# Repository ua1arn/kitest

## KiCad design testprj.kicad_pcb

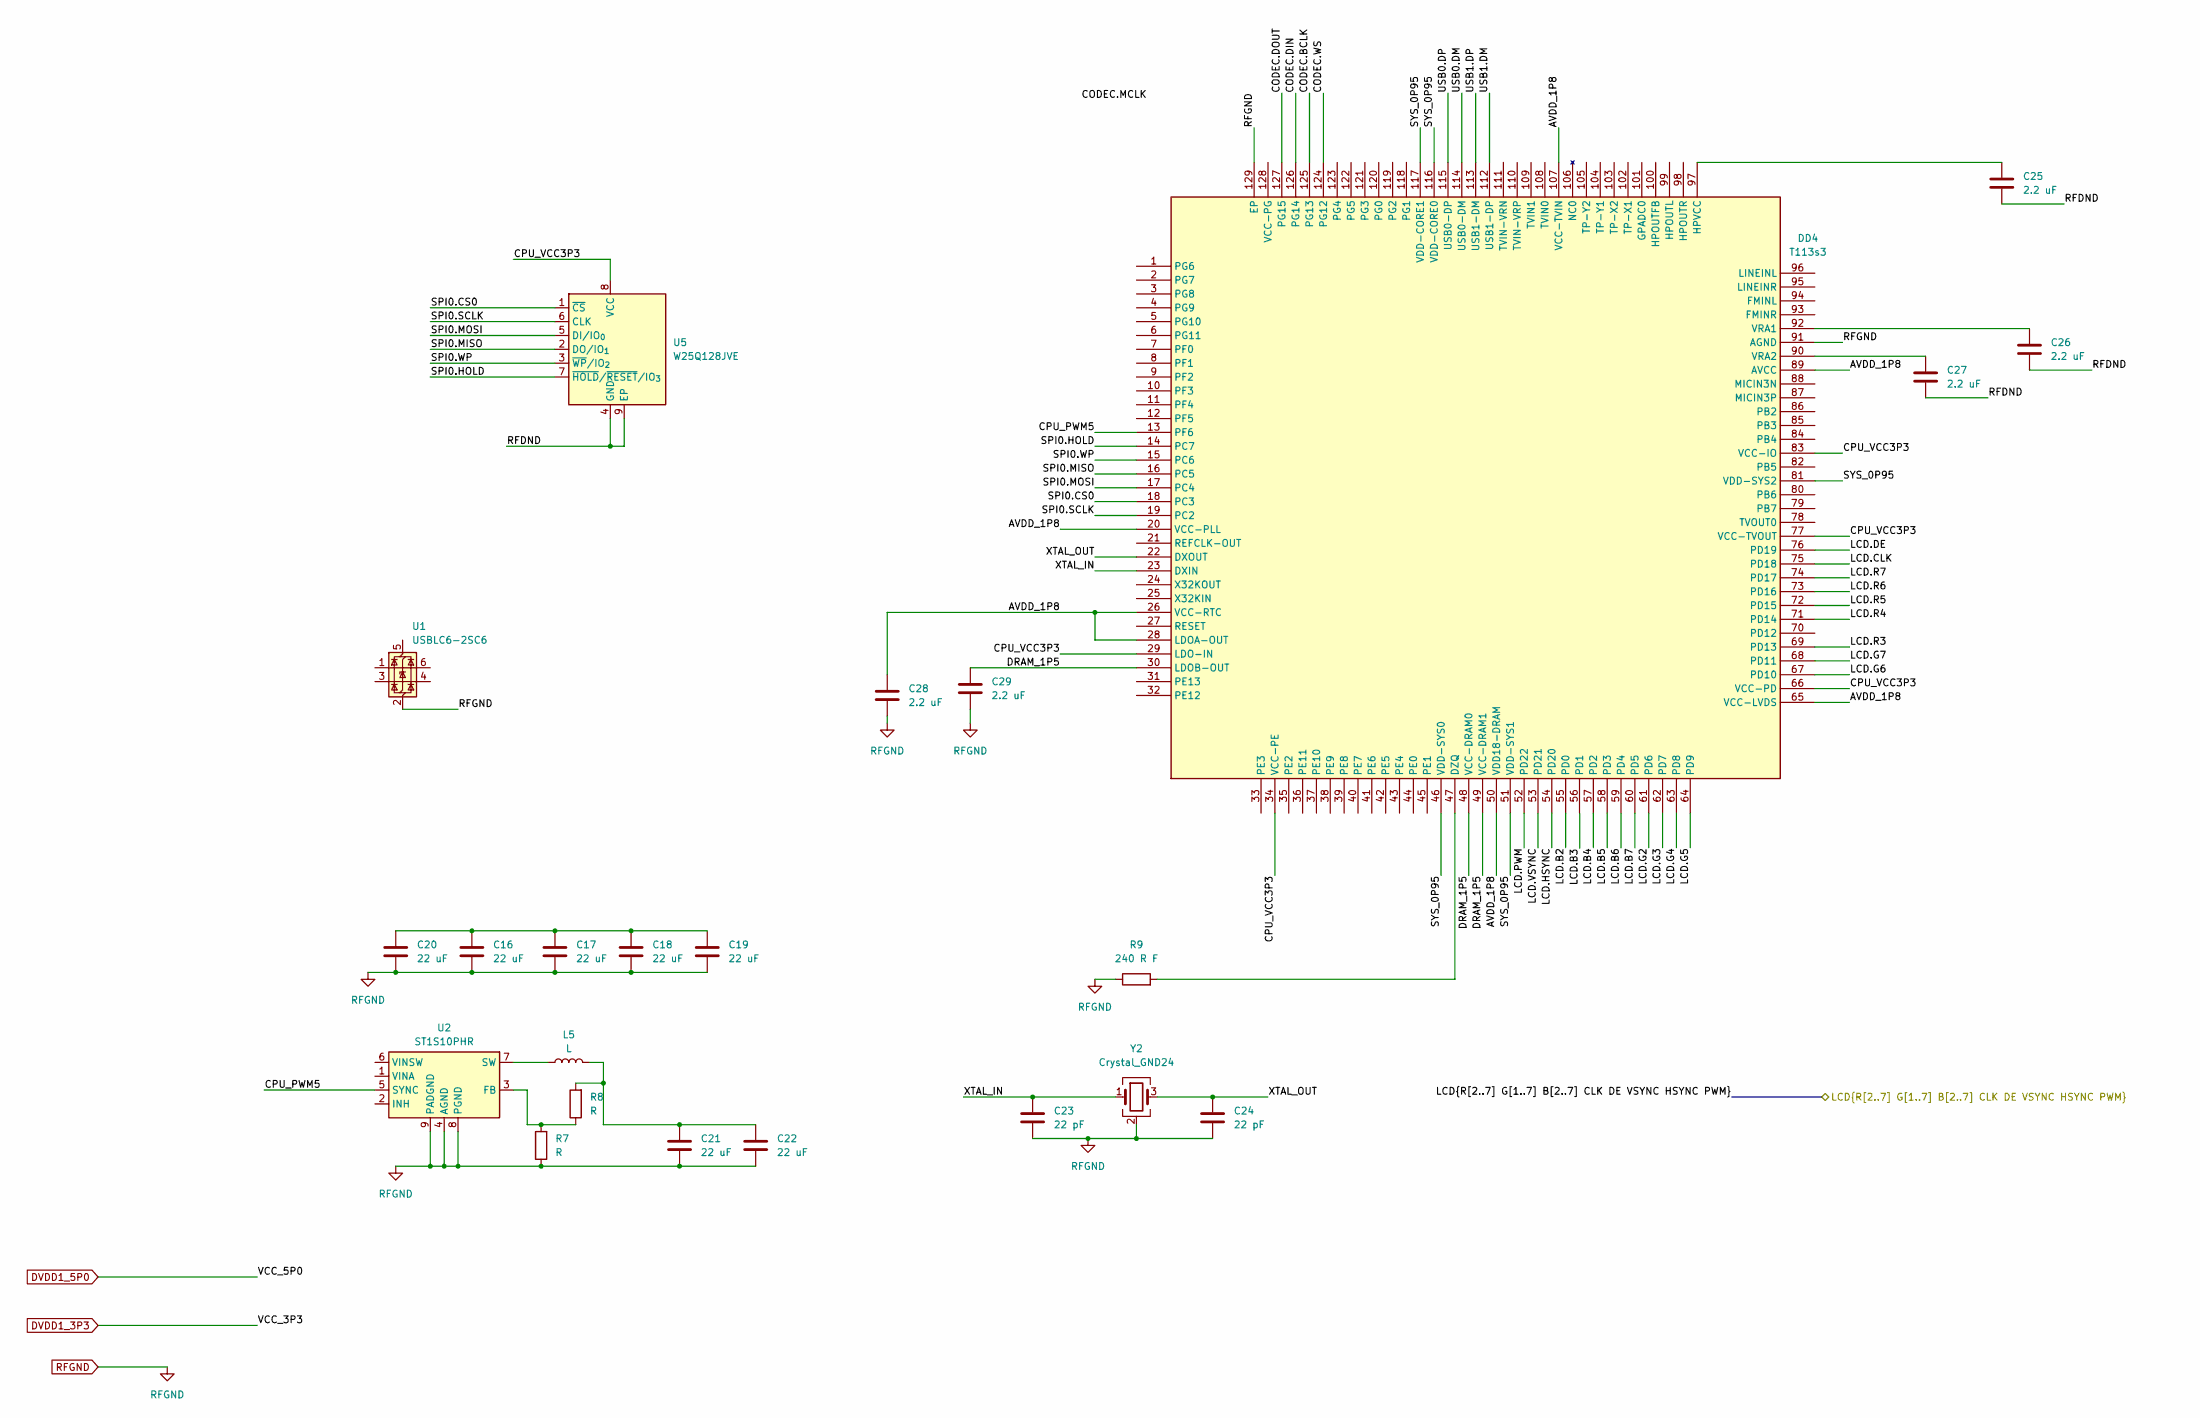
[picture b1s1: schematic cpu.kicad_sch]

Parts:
C16, C17, C18, C19, C20, C21, C22: 22 uF; C_1206_3216Metric_Pad1.33x1.80mm_HandSolder
C23, C24: 22 pF; C_0805_2012Metric_Pad1.18x1.45mm_HandSolder
C25, C26, C27, C28, C29: 2.2 uF; C_0805_2012Metric_Pad1.18x1.45mm_HandSolder
DD4: T113s3; TQFP-128_14x14mm_P0.4mm_EP8x8mm
L5: L; L_TDK_VLS6045EX_VLS6045AF
R7, R8: R; R_0805_2012Metric_Pad1.20x1.40mm_HandSolder
R9: 240 R F; R_0805_2012Metric_Pad1.20x1.40mm_HandSolder
U1: USBLC6-2SC6; SOT-23-6
U2: ST1S10PHR; TI_SO-PowerPAD-8
U5: W25Q128JVE; WSON-8-1EP_8x6mm_P1.27mm_EP3.4x4.3mm
Y2: Crystal_GND24; Crystal_SMD_7050-4Pin_7.0x5.0mm

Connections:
/cpu/AVDD_1P8: C28.1, DD4.20 (VCC-PLL), DD4.26 (VCC-RTC), DD4.28 (LDOA-OUT), DD4.50 (VDD18-DRAM), DD4.65 (VCC-LVDS), DD4.89 (AVCC), DD4.107 (VCC-TVIN)
/cpu/CODEC.BCLK: DD4.125 (PG13)
/cpu/CODEC.DIN: DD4.126 (PG14)
/cpu/CODEC.DOUT: DD4.127 (PG15)
/cpu/CODEC.WS: DD4.124 (PG12)
/cpu/CPU_PWM5: DD4.13 (PF6), U2.5 (SYNC)
/cpu/CPU_VCC3P3: DD4.29 (LDO-IN), DD4.34 (VCC-PE), DD4.66 (VCC-PD), DD4.77 (VCC-TVOUT), DD4.83 (VCC-IO), U5.8 (VCC)
/cpu/DRAM_1P5: C29.1, DD4.30 (LDOB-OUT), DD4.48 (VCC-DRAM0), DD4.49 (VCC-DRAM1)
/cpu/LCD.B4: DD4.57 (PD2); also elsewhere on the board
/cpu/LCD.B5: DD4.58 (PD3); also elsewhere on the board
/cpu/LCD.B6: DD4.59 (PD4); also elsewhere on the board
/cpu/LCD.B7: DD4.55 (PD0), DD4.60 (PD5); also elsewhere on the board
/cpu/LCD.CLK: DD4.75 (PD18); also elsewhere on the board
/cpu/LCD.DE: DD4.76 (PD19); also elsewhere on the board
/cpu/LCD.G2: DD4.61 (PD6); also elsewhere on the board
/cpu/LCD.G3: DD4.62 (PD7); also elsewhere on the board
/cpu/LCD.G4: DD4.63 (PD8); also elsewhere on the board
/cpu/LCD.G5: DD4.64 (PD9); also elsewhere on the board
/cpu/LCD.G6: DD4.67 (PD10); also elsewhere on the board
/cpu/LCD.G7: DD4.68 (PD11); also elsewhere on the board
/cpu/LCD.HSYNC: DD4.54 (PD20); also elsewhere on the board
/cpu/LCD.PWM: DD4.52 (PD22); also elsewhere on the board
/cpu/LCD.R3: DD4.69 (PD13); also elsewhere on the board
/cpu/LCD.R4: DD4.71 (PD14); also elsewhere on the board
/cpu/LCD.R5: DD4.72 (PD15); also elsewhere on the board
/cpu/LCD.R6: DD4.73 (PD16); also elsewhere on the board
/cpu/LCD.R7: DD4.74 (PD17); also elsewhere on the board
/cpu/LCD.VSYNC: DD4.53 (PD21); also elsewhere on the board
/cpu/RFDND: C25.2, C26.2, C27.2, U5.4 (GND), U5.9 (EP)
/cpu/SPI0.CS0: DD4.18 (PC3), U5.1 (~CS)
/cpu/SPI0.HOLD: DD4.14 (PC7), U5.7 (~HOLD/~RESET/IO_{3})
/cpu/SPI0.MISO: DD4.16 (PC5), U5.2 (DO/IO_{1})
/cpu/SPI0.MOSI: DD4.17 (PC4), U5.5 (DI/IO_{0})
/cpu/SPI0.SCLK: DD4.19 (PC2), U5.6 (CLK)
/cpu/SPI0.WP: DD4.15 (PC6), U5.3 (~WP/IO_{2})
/cpu/SYS_0P95: DD4.46 (VDD-SYS0), DD4.51 (VDD-SYS1), DD4.81 (VDD-SYS2), DD4.116 (VDD-CORE0), DD4.117 (VDD-CORE1)
/cpu/USB0.DM: DD4.114 (USB0-DM)
/cpu/USB0.DP: DD4.115 (USB0-DP)
/cpu/USB1.DM: DD4.112 (USB1-DP)
/cpu/USB1.DP: DD4.113 (USB1-DM)
/cpu/XTAL_IN: C23.1, DD4.23 (DXIN), Y2.1
/cpu/XTAL_OUT: C24.1, DD4.22 (DXOUT), Y2.3
unnamed: C16.2, C17.2, C18.2, C19.2, C20.2
unnamed: C21.2, C22.2, L5.2, R8.2
unnamed: DD4.47 (DZQ), R9.2
unnamed: C25.1, DD4.97 (HPVCC)
unnamed: C26.1, DD4.92 (VRA1)
unnamed: C27.1, DD4.90 (VRA2)
unnamed: R7.2, R8.1, U2.3 (FB)
unnamed: L5.1, U2.7 (SW)
RFGND: C16.1, C17.1, C18.1, C19.1, C20.1, C21.1, C22.1, C23.2, C24.2, C28.2, C29.2, DD4.91 (AGND), DD4.129 (EP), R7.1, R9.1, U1.2 (GND_2), U2.4 (AGND), U2.8 (PGND), U2.9 (PADGND), Y2.2 (G), Y2.4 (G); also elsewhere on the board

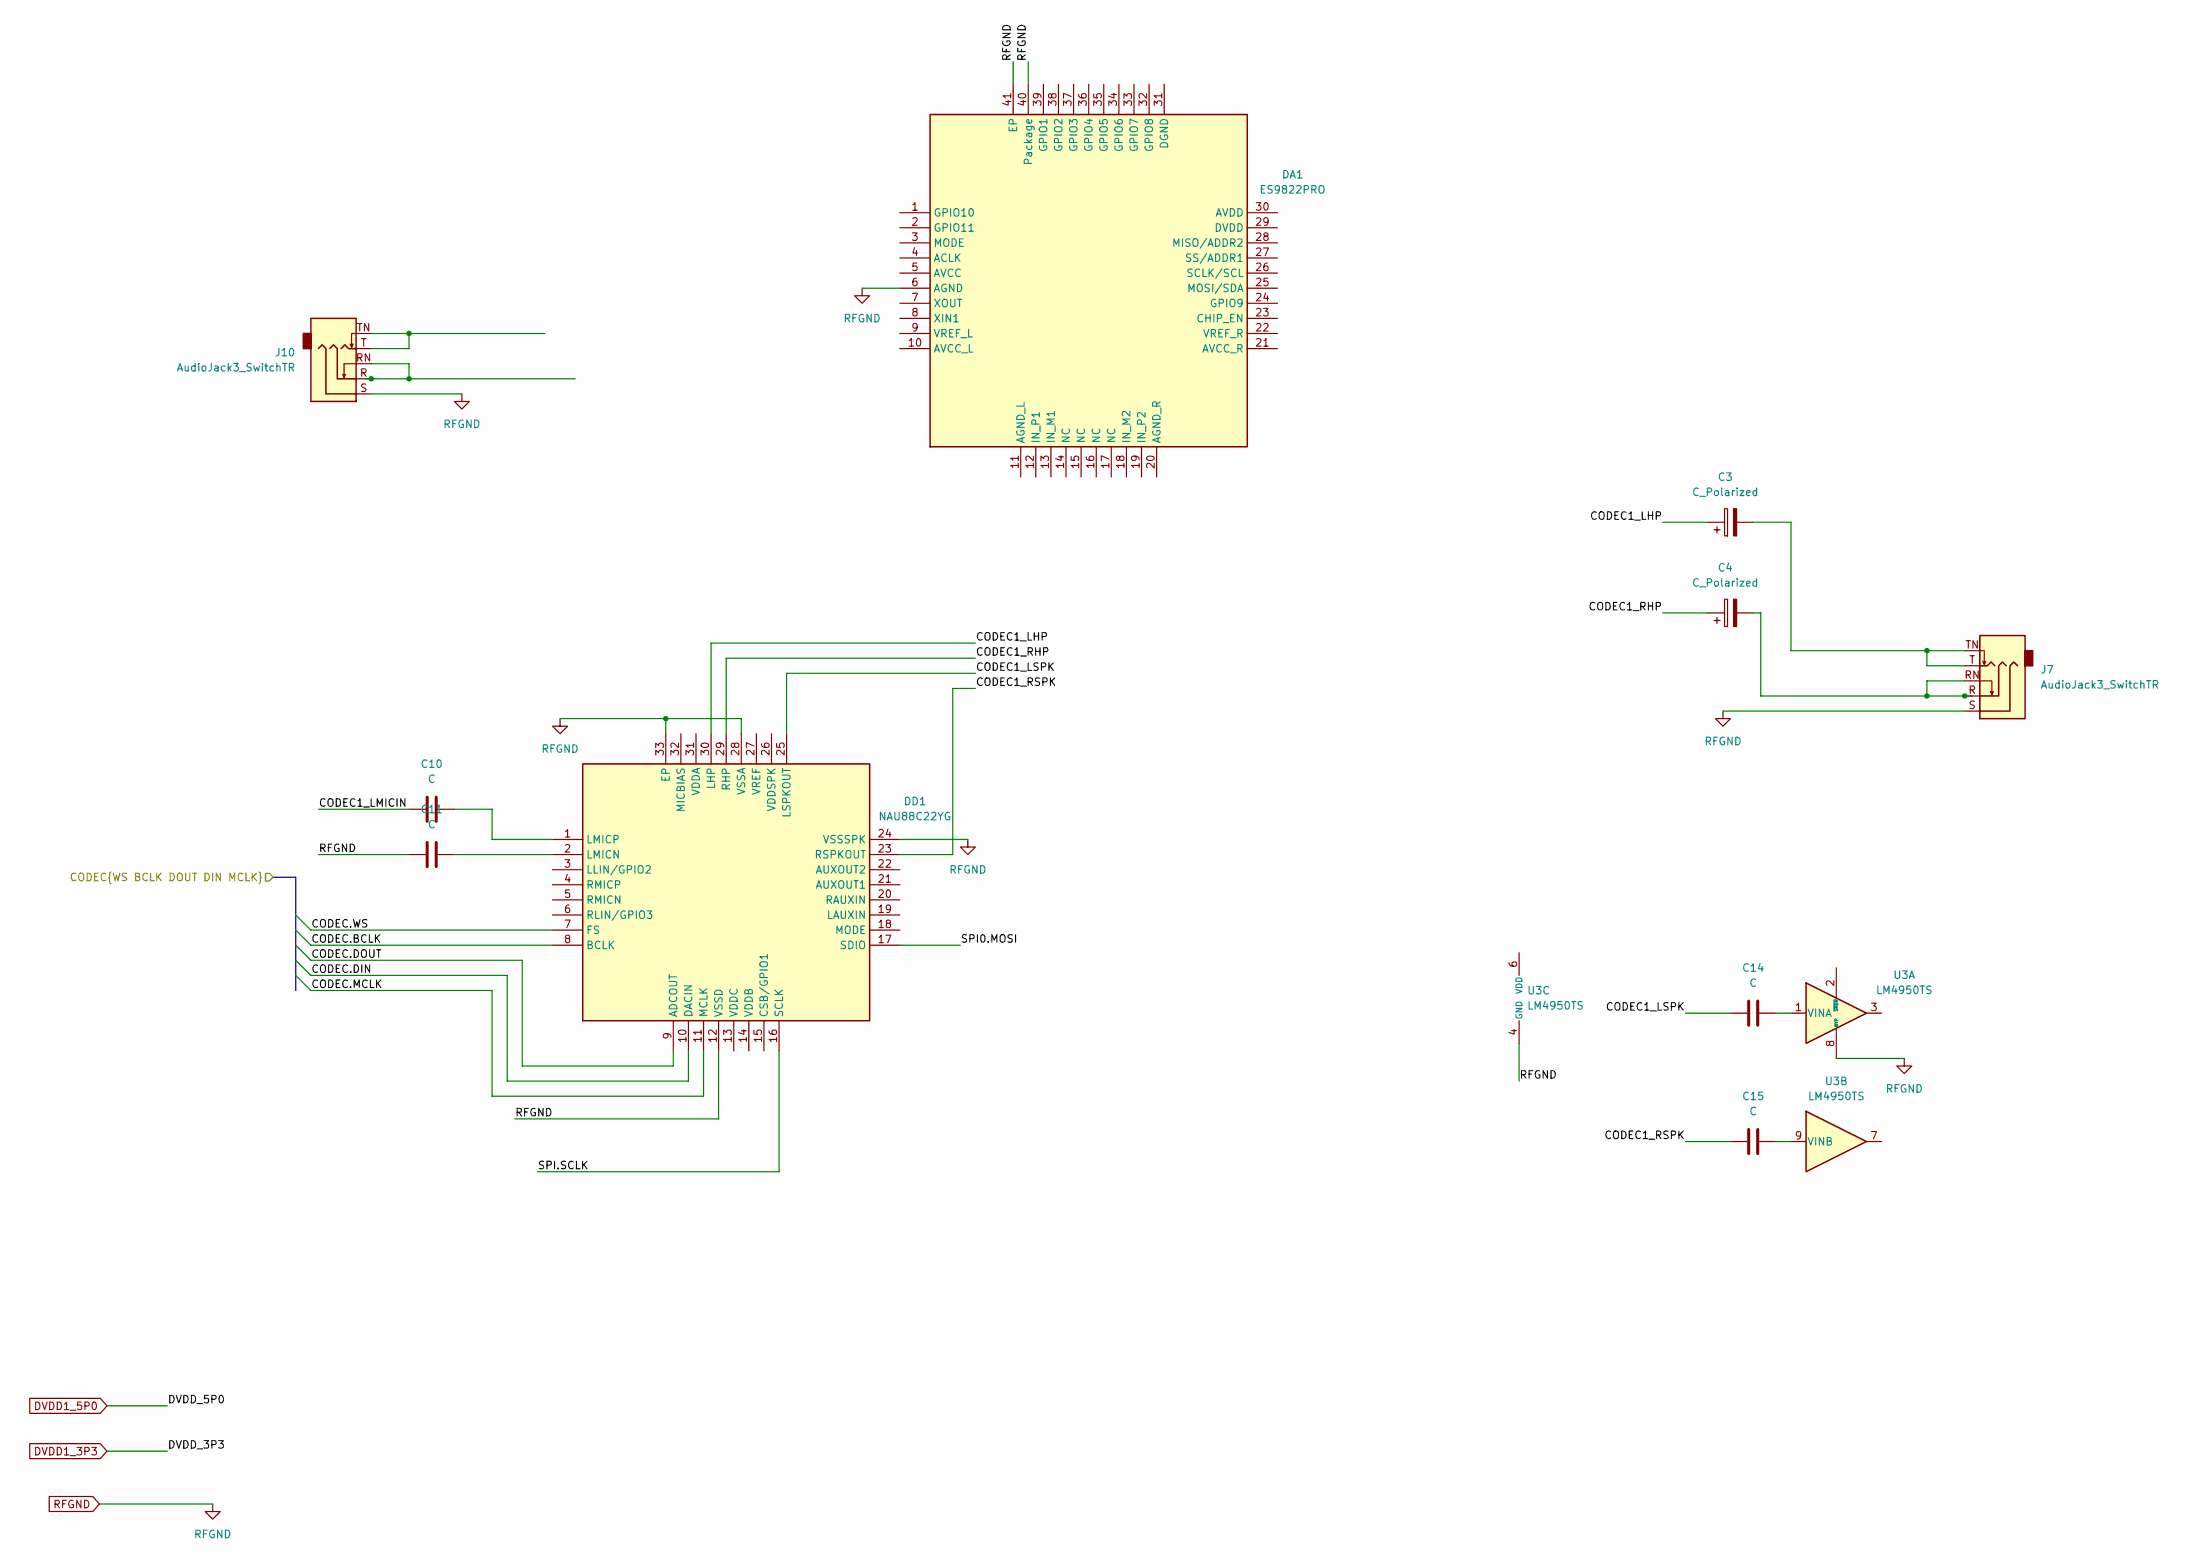
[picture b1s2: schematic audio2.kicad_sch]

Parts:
C3, C4: C_Polarized; CP_Elec_6.3x5.4
C10, C11, C14, C15: C; C_0805_2012Metric_Pad1.18x1.45mm_HandSolder
DA1: ES9822PRO; QFN-40-1EP_6x6mm_P0.5mm_EP4.6x4.6mm_ThermalVias
DD1: NAU88C22YG; TQFN-32-1EP_5x5mm_P0.5mm_EP3.1x3.1mm_ThermalVias
J7, J10: AudioJack3_SwitchTR; Jack_3.5mm_CUI_SJ2-3593D-SMT_Horizontal
U3: LM4950TS; TO-263-9_TabPin5

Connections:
/audio/CODEC1_LHP: C3.1, DD1.30 (LHP)
/audio/CODEC1_LMICIN: C10.2
/audio/CODEC1_LSPK: C14.2, DD1.25 (LSPKOUT)
/audio/CODEC1_RHP: C4.1, DD1.29 (RHP)
/audio/CODEC1_RSPK: C15.2, DD1.23 (RSPKOUT)
/audio/CODEC.BCLK: DD1.8 (BCLK)
/audio/CODEC.DIN: DD1.10 (DACIN)
/audio/CODEC.DOUT: DD1.9 (ADCOUT)
/audio/CODEC.MCLK: DD1.11 (MCLK)
/audio/CODEC.WS: DD1.7 (FS)
/audio/SPI0.MOSI: DD1.17 (SDIO)
/audio/SPI.SCLK: DD1.16 (SCLK)
unnamed: C3.2, J7.T, J7.TN
unnamed: C4.2, J7.R, J7.RN
unnamed: C11.1, DD1.2 (LMICN)
unnamed: C10.1, DD1.1 (LMICP)
unnamed: J10.R, J10.RN
unnamed: J10.T, J10.TN
unnamed: C14.1, U3.1 (VINA)
unnamed: C15.1, U3.9 (VINB)
RFGND: C11.2, DA1.6 (AGND), DA1.40 (Package), DA1.41 (EP), DD1.12 (VSSD), DD1.24 (VSSSPK), DD1.28 (VSSA), DD1.33 (EP), J7.S, J10.S, U3.4 (GND), U3.5 (GND), U3.8 (BYP); also elsewhere on the board

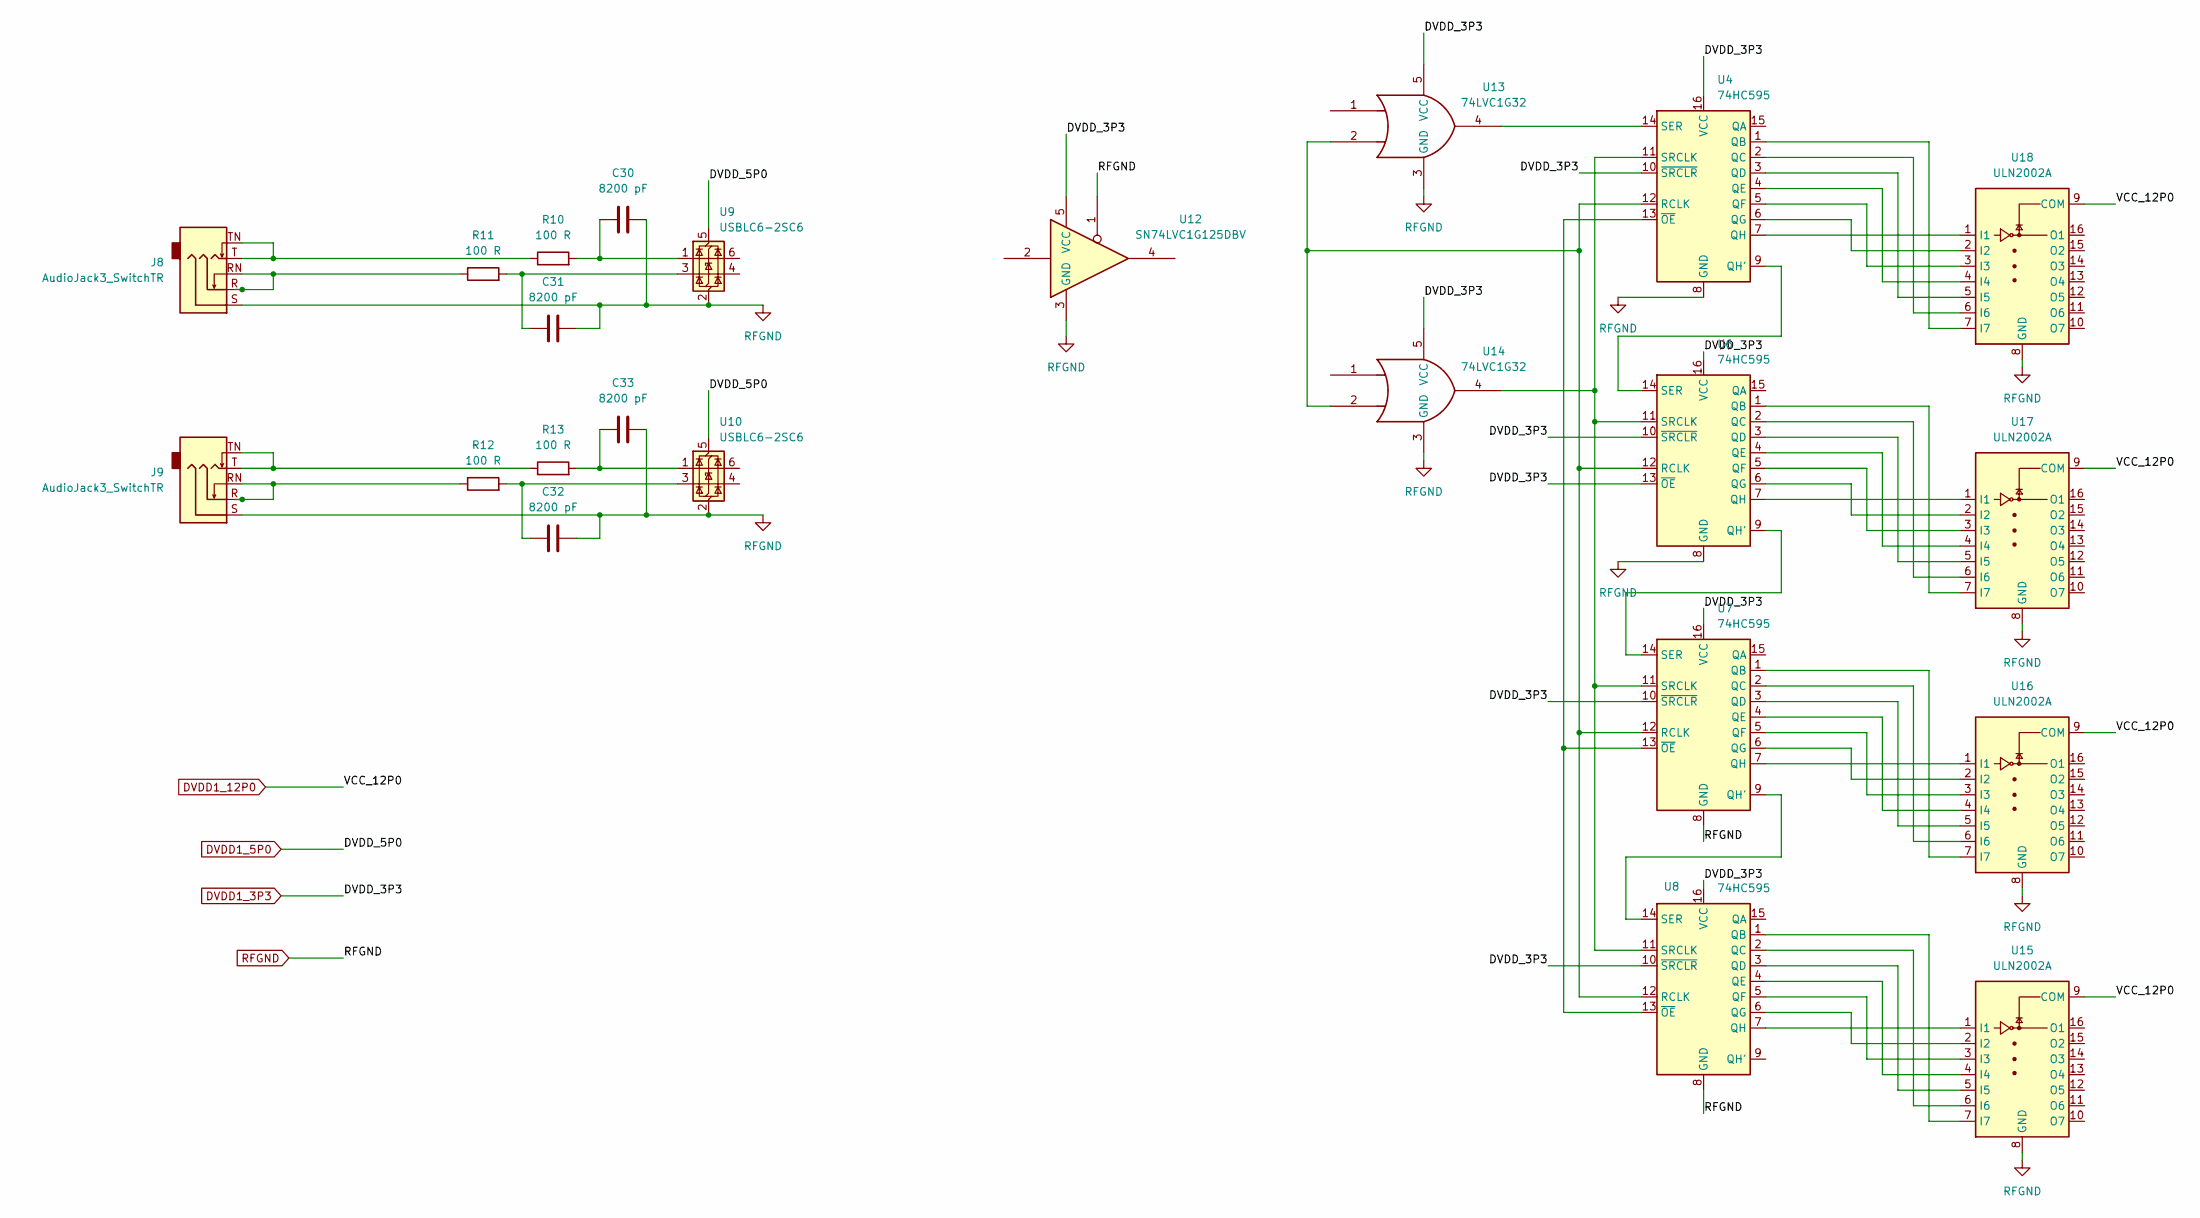
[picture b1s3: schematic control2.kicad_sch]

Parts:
C30, C31, C32, C33: 8200 pF; C_0805_2012Metric_Pad1.18x1.45mm_HandSolder
J8, J9: AudioJack3_SwitchTR; Jack_3.5mm_CUI_SJ2-3593D-SMT_Horizontal
R10, R11, R12, R13: 100 R; R_0805_2012Metric_Pad1.20x1.40mm_HandSolder
U4, U6, U7, U8: 74HC595; TSSOP-16_4.4x5mm_P0.65mm
U9, U10: USBLC6-2SC6; SOT-23-6
U12: SN74LVC1G125DBV; SOT-23-5
U13, U14: 74LVC1G32; SOT-23-5
U15, U16, U17, U18: ULN2002A; TSSOP-16_4.4x5mm_P0.65mm

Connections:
DVDD1_3P3: U4.10 (~SRCLR), U4.16 (VCC), U6.10 (~SRCLR), U6.13 (~OE), U6.16 (VCC), U7.10 (~SRCLR), U7.16 (VCC), U8.10 (~SRCLR), U8.16 (VCC), U12.5 (VCC), U13.5 (VCC), U14.5 (VCC); also elsewhere on the board
DVDD1_5P0: U9.5 (VBUS), U10.5 (VBUS)
DVDD1_12P0: U15.9 (COM), U16.9 (COM), U17.9 (COM), U18.9 (COM)
unnamed: C30.1, R10.2, U9.1 (I/O1)
unnamed: C31.2, R11.2, U9.3 (I/O2)
unnamed: C32.2, R12.2, U10.3 (I/O2)
unnamed: C33.1, R13.2, U10.1 (I/O1)
unnamed: J8.R, J8.RN, R11.1
unnamed: J8.T, J8.TN, R10.1
unnamed: J9.R, J9.RN, R12.1
unnamed: J9.T, J9.TN, R13.1
unnamed: U4.9 (QH'), U6.14 (SER)
unnamed: U4.12 (RCLK), U6.12 (RCLK), U7.12 (RCLK), U8.12 (RCLK), U13.2, U14.2
unnamed: U4.14 (SER), U13.4
unnamed: U4.11 (SRCLK), U6.11 (SRCLK), U7.11 (SRCLK), U8.11 (SRCLK), U14.4
unnamed: U4.13 (~OE), U7.13 (~OE), U8.13 (~OE)
unnamed: U6.9 (QH'), U7.14 (SER)
unnamed: U7.9 (QH'), U8.14 (SER)
unnamed: U8.7 (QH), U15.1 (I1)
unnamed: U8.6 (QG), U15.2 (I2)
unnamed: U8.5 (QF), U15.3 (I3)
unnamed: U8.4 (QE), U15.4 (I4)
unnamed: U8.3 (QD), U15.5 (I5)
unnamed: U8.2 (QC), U15.6 (I6)
unnamed: U8.1 (QB), U15.7 (I7)
unnamed: U7.7 (QH), U16.1 (I1)
unnamed: U7.6 (QG), U16.2 (I2)
unnamed: U7.5 (QF), U16.3 (I3)
unnamed: U7.4 (QE), U16.4 (I4)
unnamed: U7.3 (QD), U16.5 (I5)
unnamed: U7.2 (QC), U16.6 (I6)
unnamed: U7.1 (QB), U16.7 (I7)
unnamed: U6.7 (QH), U17.1 (I1)
unnamed: U6.6 (QG), U17.2 (I2)
unnamed: U6.5 (QF), U17.3 (I3)
unnamed: U6.4 (QE), U17.4 (I4)
unnamed: U6.3 (QD), U17.5 (I5)
unnamed: U6.2 (QC), U17.6 (I6)
unnamed: U6.1 (QB), U17.7 (I7)
unnamed: U4.7 (QH), U18.1 (I1)
unnamed: U4.6 (QG), U18.2 (I2)
unnamed: U4.5 (QF), U18.3 (I3)
unnamed: U4.4 (QE), U18.4 (I4)
unnamed: U4.3 (QD), U18.5 (I5)
unnamed: U4.2 (QC), U18.6 (I6)
unnamed: U4.1 (QB), U18.7 (I7)
RFGND: C30.2, C31.1, C32.1, C33.2, J8.S, J9.S, U4.8 (GND), U6.8 (GND), U7.8 (GND), U8.8 (GND), U9.2 (GND), U10.2 (GND), U12.1, U12.3 (GND), U13.3 (GND), U14.3 (GND), U15.8 (GND), U16.8 (GND), U17.8 (GND), U18.8 (GND); also elsewhere on the board

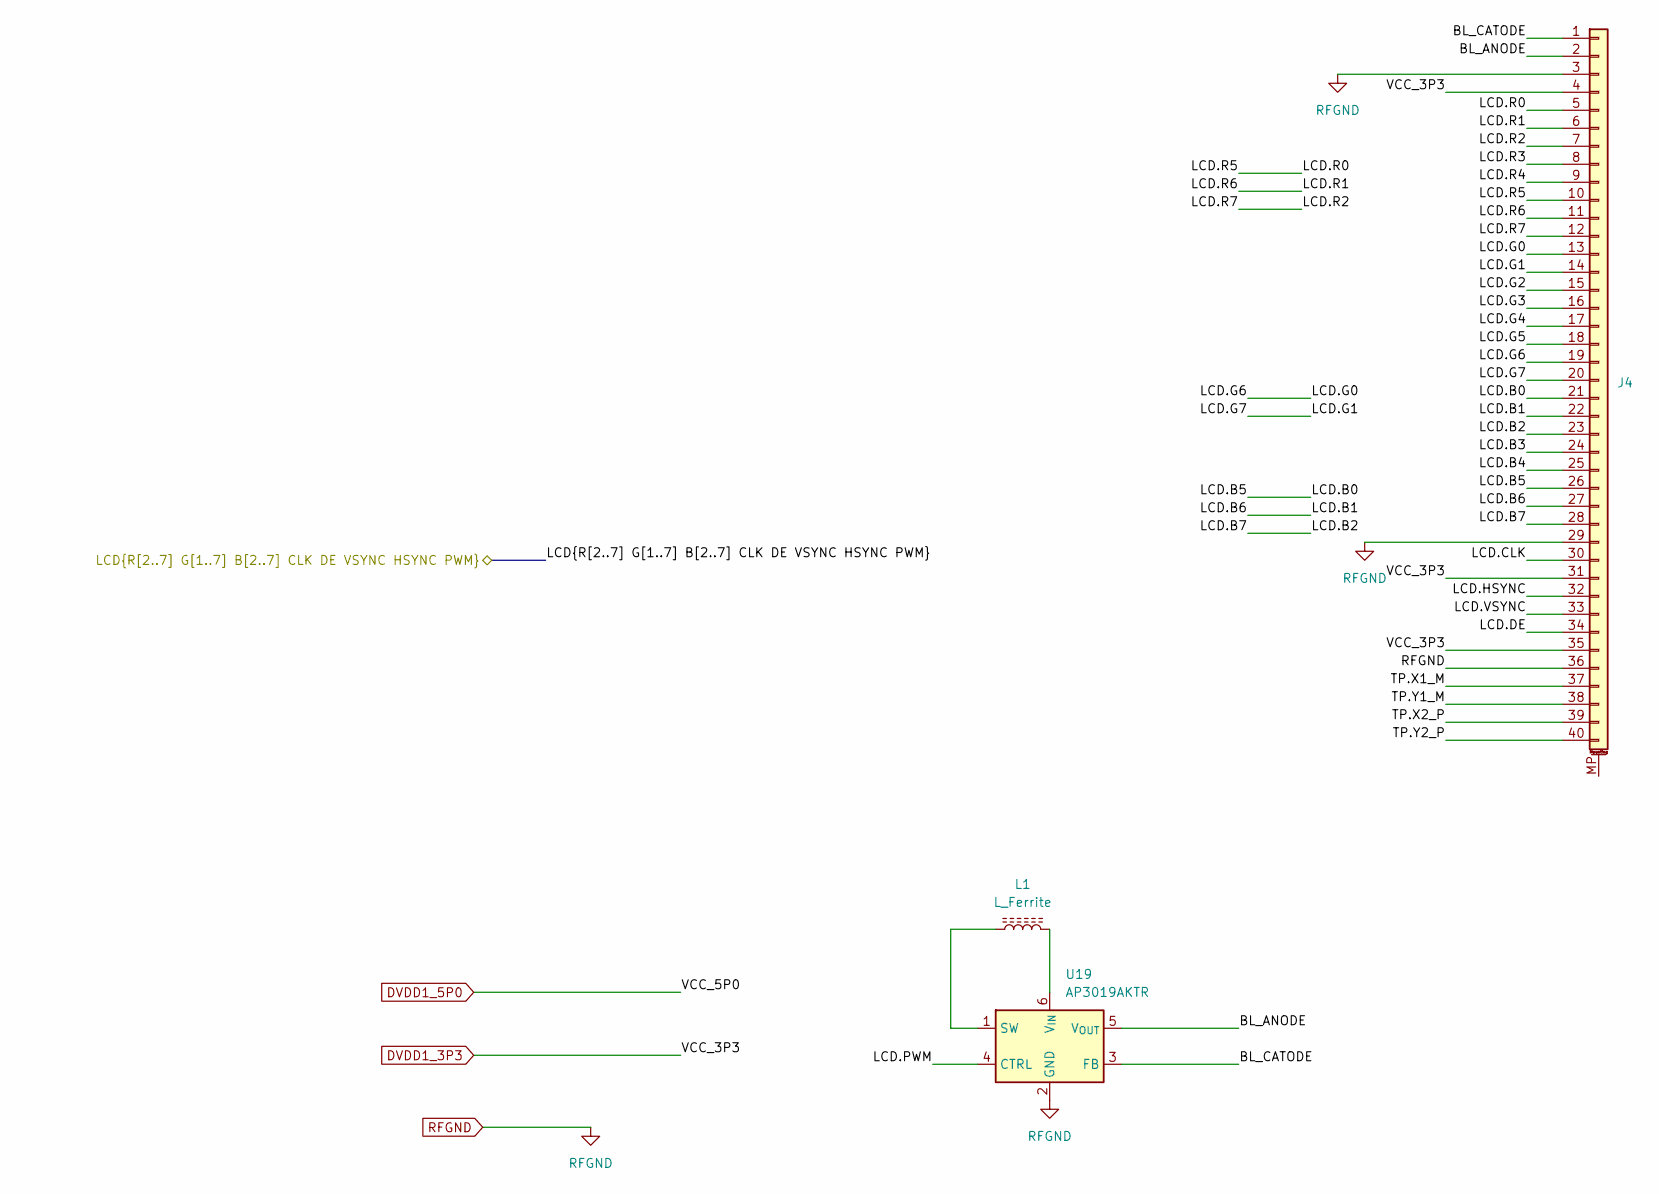
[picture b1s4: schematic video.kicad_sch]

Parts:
J4: Conn_01x40_MountingPin; Amphenol_F32R-1A7x1-11040_1x40-1MP_P0.5mm_Horizontal
L1: L_Ferrite; L_7.3x7.3_H4.5
U19: AP3019AKTR; SOT-23-6

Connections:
/cpu/LCD.B3: J4.24
/cpu/LCD.B4: J4.25; also elsewhere on the board
/cpu/LCD.B5: J4.21, J4.26; also elsewhere on the board
/cpu/LCD.B6: J4.22, J4.27; also elsewhere on the board
/cpu/LCD.B7: J4.23, J4.28; also elsewhere on the board
/cpu/LCD.CLK: J4.30; also elsewhere on the board
/cpu/LCD.DE: J4.34; also elsewhere on the board
/cpu/LCD.G2: J4.15; also elsewhere on the board
/cpu/LCD.G3: J4.16; also elsewhere on the board
/cpu/LCD.G4: J4.17; also elsewhere on the board
/cpu/LCD.G5: J4.18; also elsewhere on the board
/cpu/LCD.G6: J4.13, J4.19; also elsewhere on the board
/cpu/LCD.G7: J4.14, J4.20; also elsewhere on the board
/cpu/LCD.HSYNC: J4.32; also elsewhere on the board
/cpu/LCD.PWM: U19.4 (CTRL); also elsewhere on the board
/cpu/LCD.R3: J4.8; also elsewhere on the board
/cpu/LCD.R4: J4.9; also elsewhere on the board
/cpu/LCD.R5: J4.5, J4.10; also elsewhere on the board
/cpu/LCD.R6: J4.6, J4.11; also elsewhere on the board
/cpu/LCD.R7: J4.7, J4.12; also elsewhere on the board
/cpu/LCD.VSYNC: J4.33; also elsewhere on the board
/video/BL_ANODE: J4.2, U19.5 (V_{OUT})
/video/BL_CATODE: J4.1, U19.3 (FB)
/video/TP.X1_M: J4.37
/video/TP.X2_P: J4.39
/video/TP.Y1_M: J4.38
/video/TP.Y2_P: J4.40
DVDD1_3P3: J4.4, J4.31, J4.35; also elsewhere on the board
unnamed: L1.1, U19.1 (SW)
unnamed: L1.2, U19.6 (V_{IN})
RFGND: J4.3, J4.29, J4.36, U19.2 (GND); also elsewhere on the board

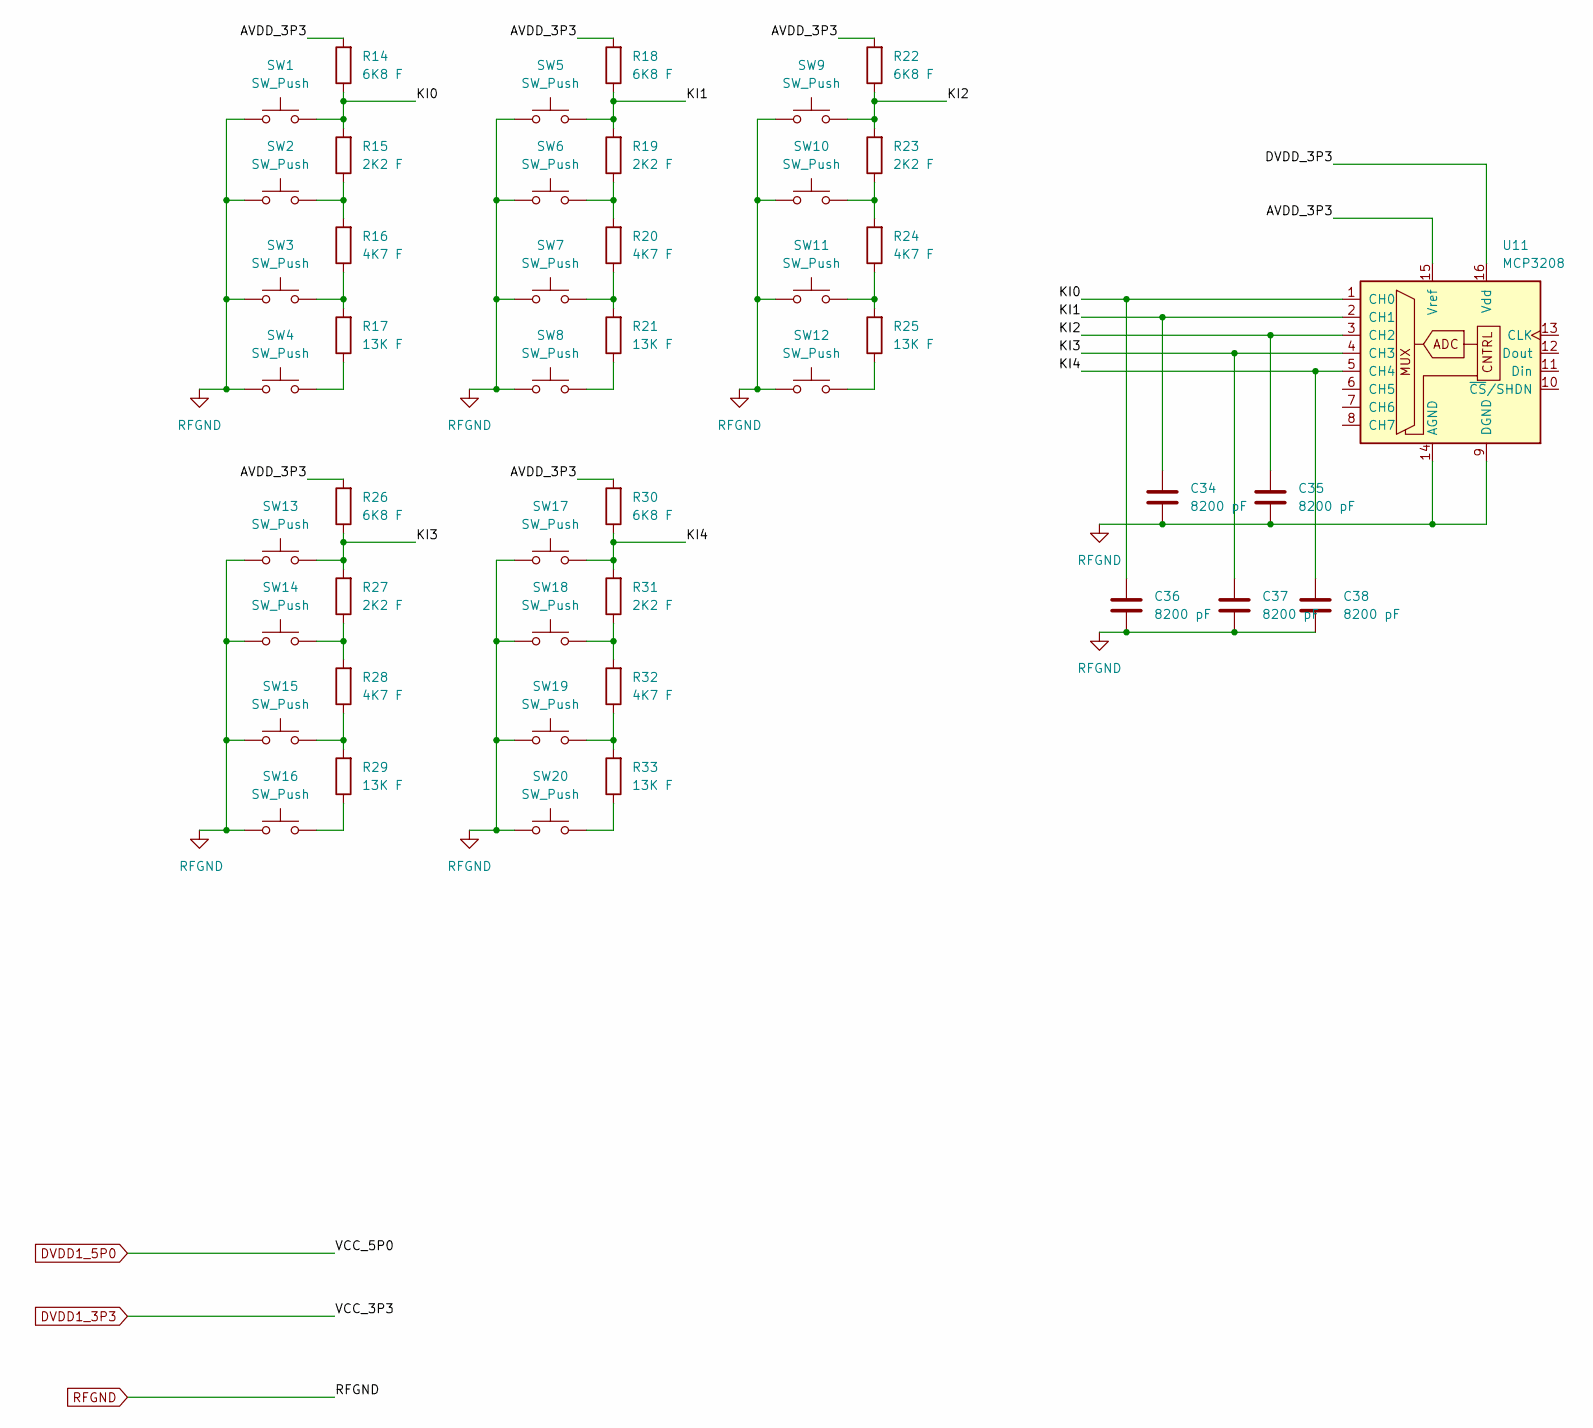
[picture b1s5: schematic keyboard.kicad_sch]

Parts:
C34, C35, C36, C37, C38: 8200 pF; C_0805_2012Metric_Pad1.18x1.45mm_HandSolder
R14, R18, R22, R26, R30: 6K8 F; R_0805_2012Metric_Pad1.20x1.40mm_HandSolder
R15, R19, R23, R27, R31: 2K2 F; R_0805_2012Metric_Pad1.20x1.40mm_HandSolder
R16, R20, R24, R28, R32: 4K7 F; R_0805_2012Metric_Pad1.20x1.40mm_HandSolder
R17, R21, R25, R29, R33: 13K F; R_0805_2012Metric_Pad1.20x1.40mm_HandSolder
SW1, SW2, SW3, SW4, SW5, SW6, SW7, SW8, SW9, SW10, SW11, SW12, SW13, SW14, SW15, SW16, SW17, SW18, SW19, SW20: SW_Push; SW_PUSH_6mm_H9.5mm
U11: MCP3208; SOIC-16_3.9x9.9mm_P1.27mm

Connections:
/keyboard/AVDD_3P3: R14.2, R18.2, R22.2, R26.2, R30.2, U11.15 (Vref)
/keyboard/DVDD_3P3: U11.16 (Vdd)
/keyboard/KI0: C36.1, R14.1, R15.2, SW1.2, U11.1 (CH0)
/keyboard/KI1: C34.1, R18.1, R19.2, SW5.2, U11.2 (CH1)
/keyboard/KI2: C35.1, R22.1, R23.2, SW9.2, U11.3 (CH2)
/keyboard/KI3: C37.1, R26.1, R27.2, SW13.2, U11.4 (CH3)
/keyboard/KI4: C38.1, R30.1, R31.2, SW17.2, U11.5 (CH4)
unnamed: R15.1, R16.2, SW2.2
unnamed: R16.1, R17.2, SW3.2
unnamed: R17.1, SW4.2
unnamed: R19.1, R20.2, SW6.2
unnamed: R20.1, R21.2, SW7.2
unnamed: R21.1, SW8.2
unnamed: R23.1, R24.2, SW10.2
unnamed: R24.1, R25.2, SW11.2
unnamed: R25.1, SW12.2
unnamed: R27.1, R28.2, SW14.2
unnamed: R28.1, R29.2, SW15.2
unnamed: R29.1, SW16.2
unnamed: R31.1, R32.2, SW18.2
unnamed: R32.1, R33.2, SW19.2
unnamed: R33.1, SW20.2
RFGND: C34.2, C35.2, C36.2, C37.2, C38.2, SW1.1, SW2.1, SW3.1, SW4.1, SW5.1, SW6.1, SW7.1, SW8.1, SW9.1, SW10.1, SW11.1, SW12.1, SW13.1, SW14.1, SW15.1, SW16.1, SW17.1, SW18.1, SW19.1, SW20.1, U11.9 (DGND), U11.14 (AGND); also elsewhere on the board

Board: 4 copper layers, 106 parts (0 on the bottom side), 126 nets, no tracks yet.

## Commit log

2026-05-20 initial upload
2026-05-23 save state
2026-05-24 Перевёл на иерархические схемы
2026-05-24 Добавил клавиатуру
2026-05-24 кнопки
2026-05-25 save state (add 1g logic)
2026-06-08 Add ES9822QPRO
2026-06-08 Add ULN2003
2026-06-09 Использование power symbols
2026-06-14 add lcd backlight chip
2026-06-15 Добавление файлов - интеграция со specctra
